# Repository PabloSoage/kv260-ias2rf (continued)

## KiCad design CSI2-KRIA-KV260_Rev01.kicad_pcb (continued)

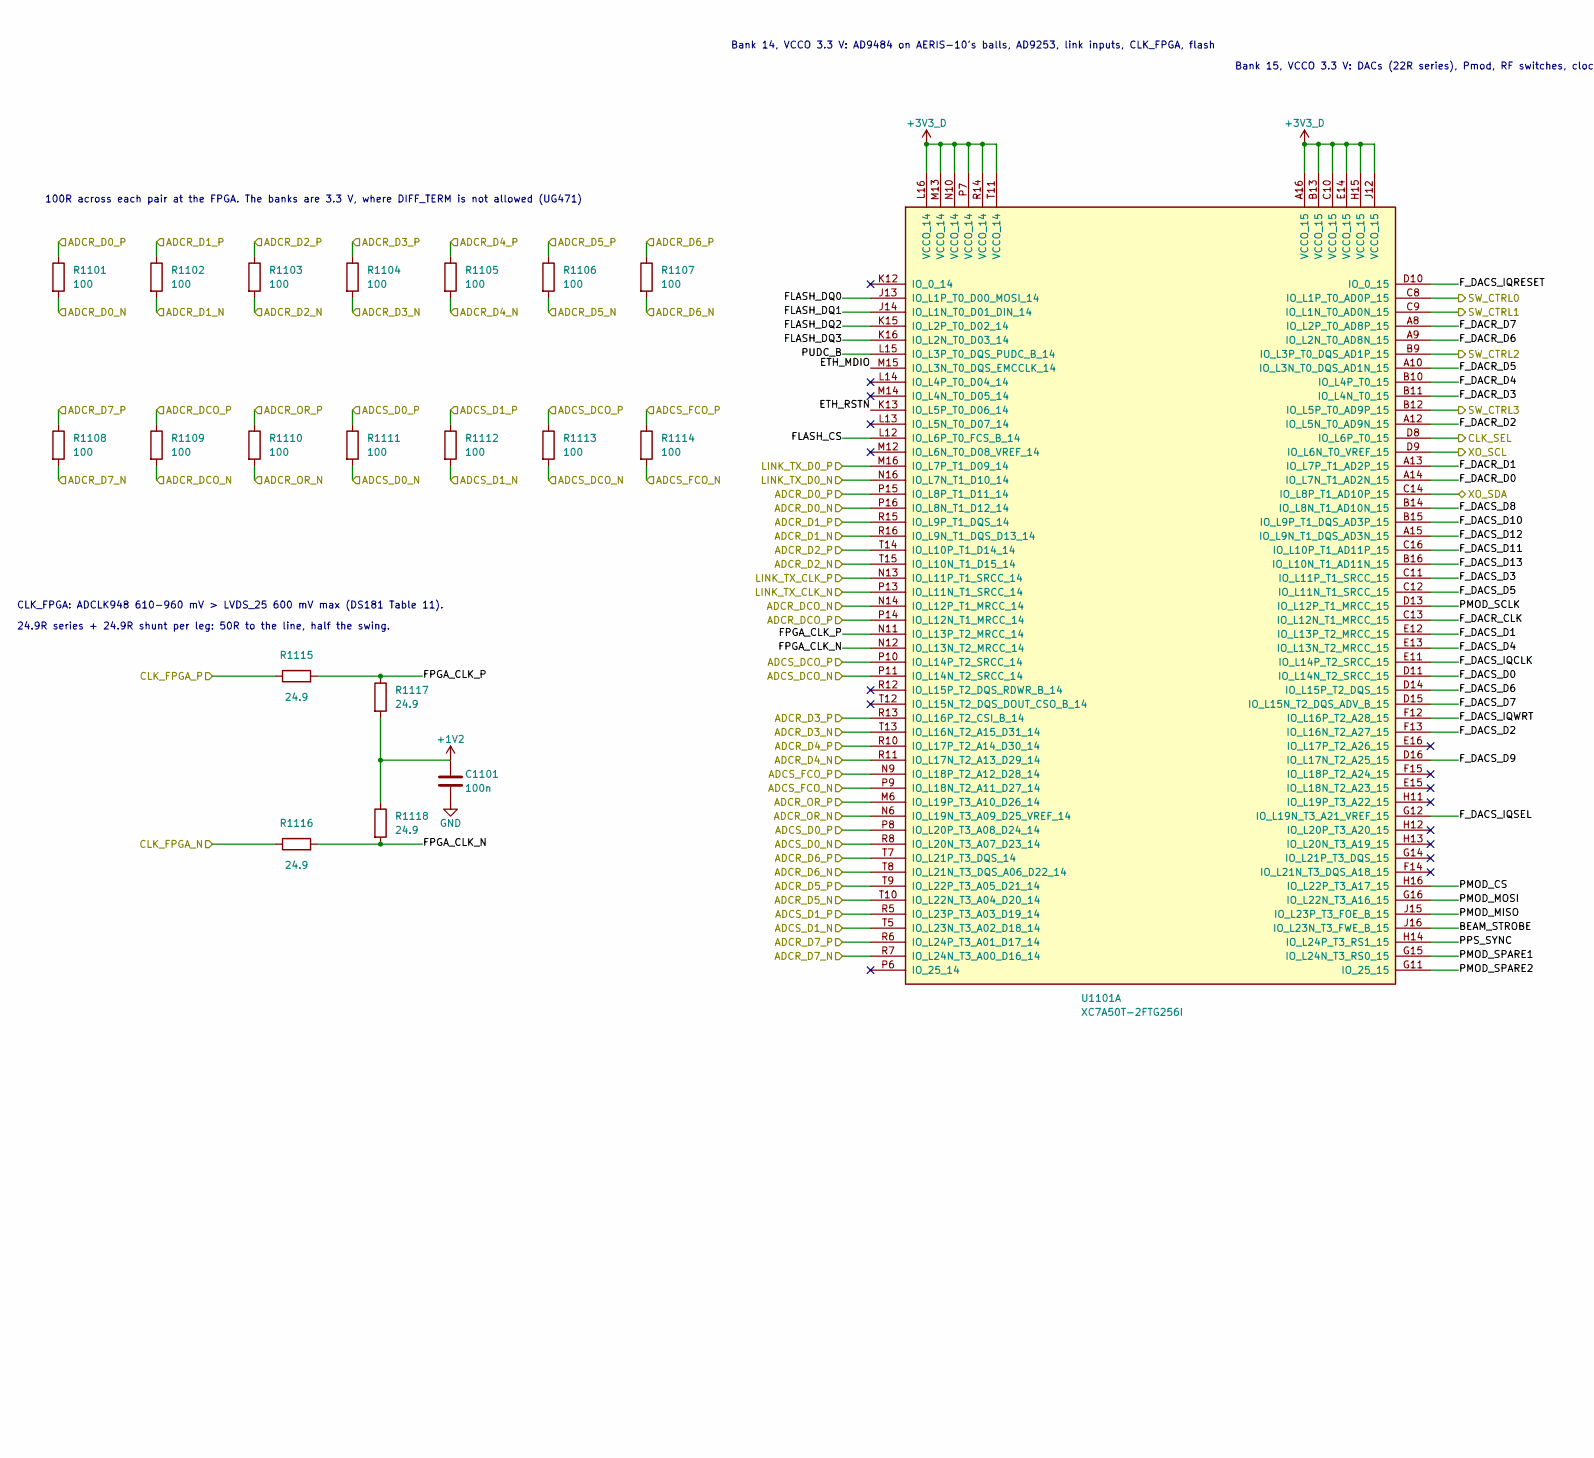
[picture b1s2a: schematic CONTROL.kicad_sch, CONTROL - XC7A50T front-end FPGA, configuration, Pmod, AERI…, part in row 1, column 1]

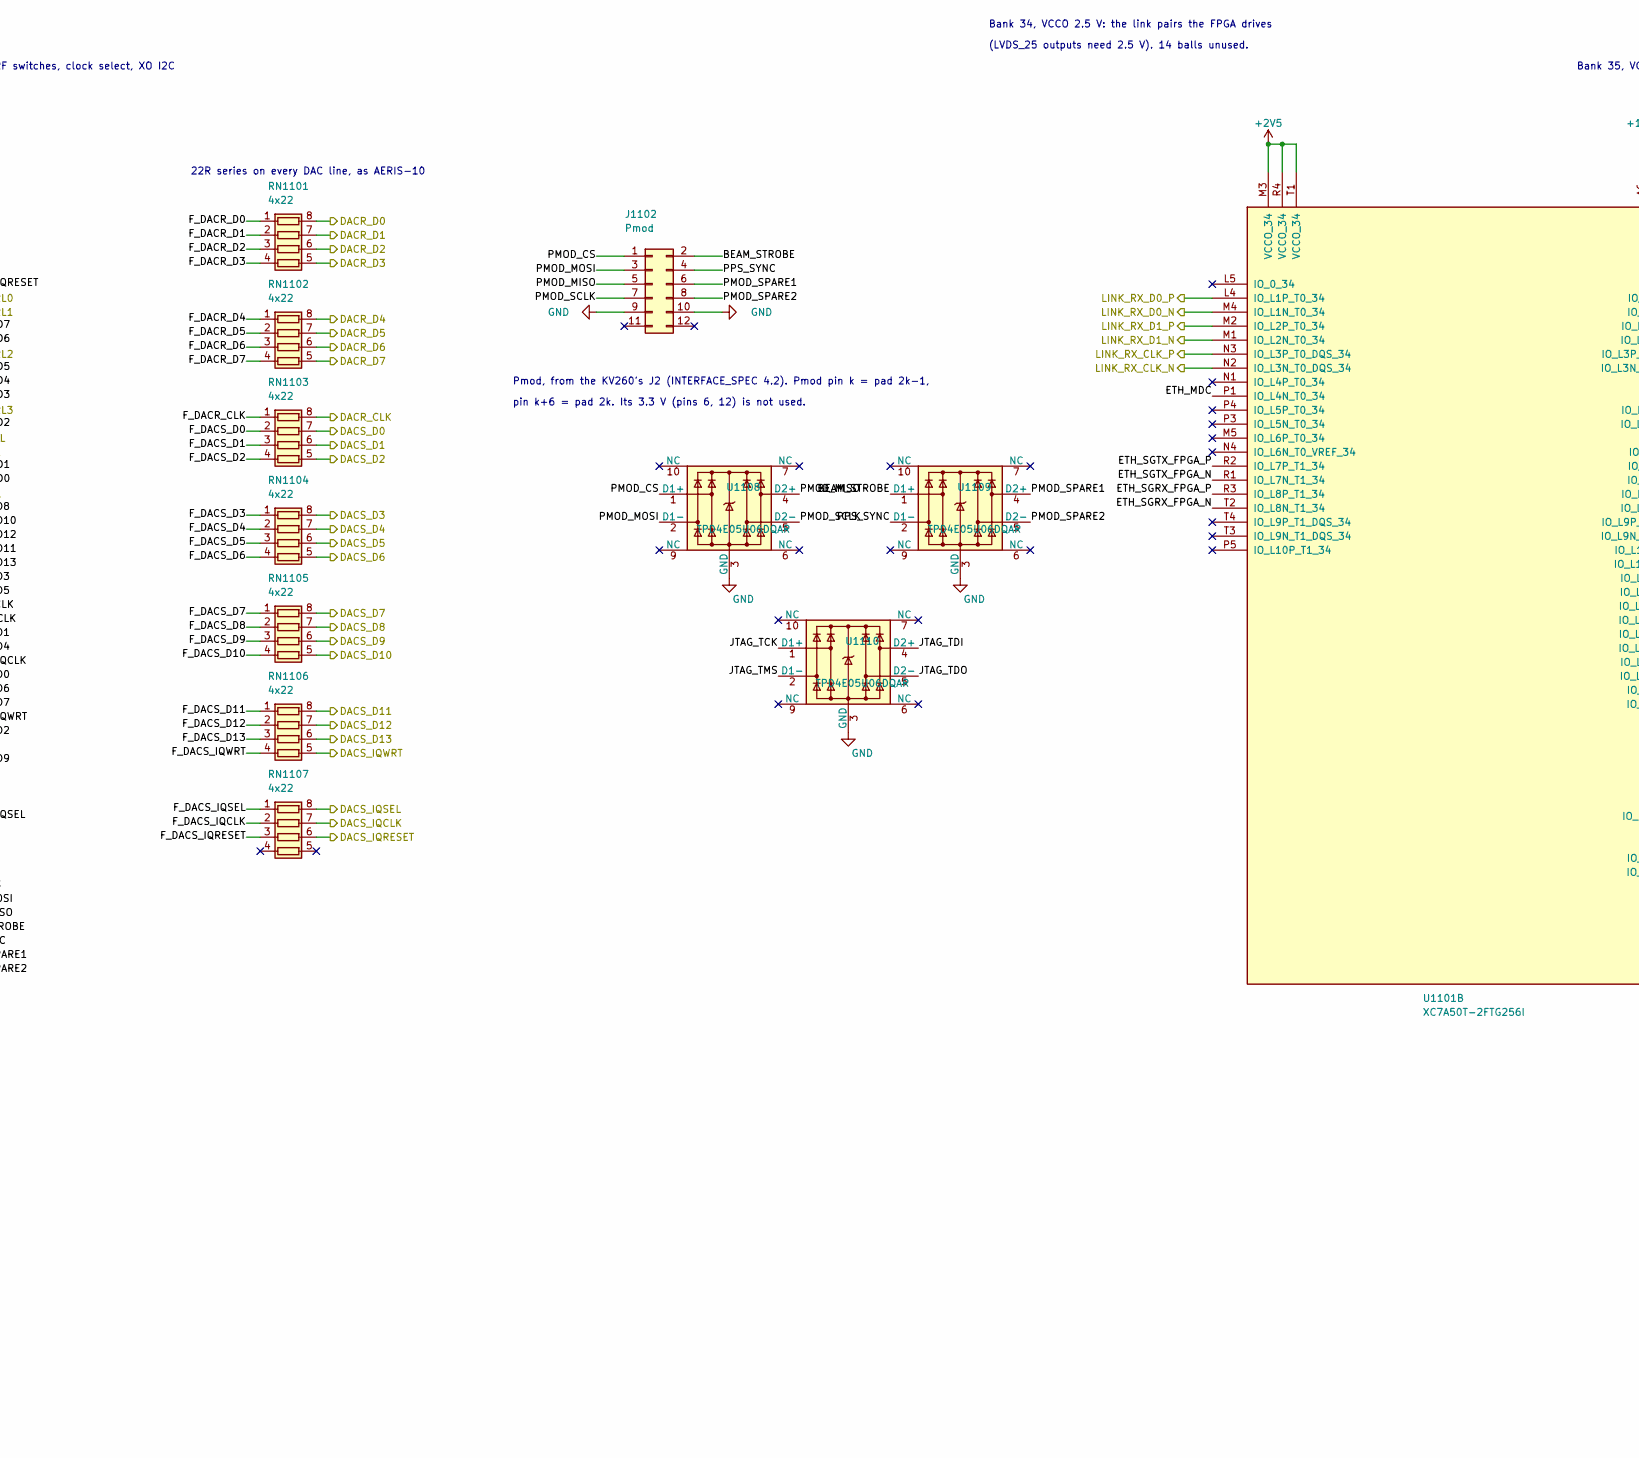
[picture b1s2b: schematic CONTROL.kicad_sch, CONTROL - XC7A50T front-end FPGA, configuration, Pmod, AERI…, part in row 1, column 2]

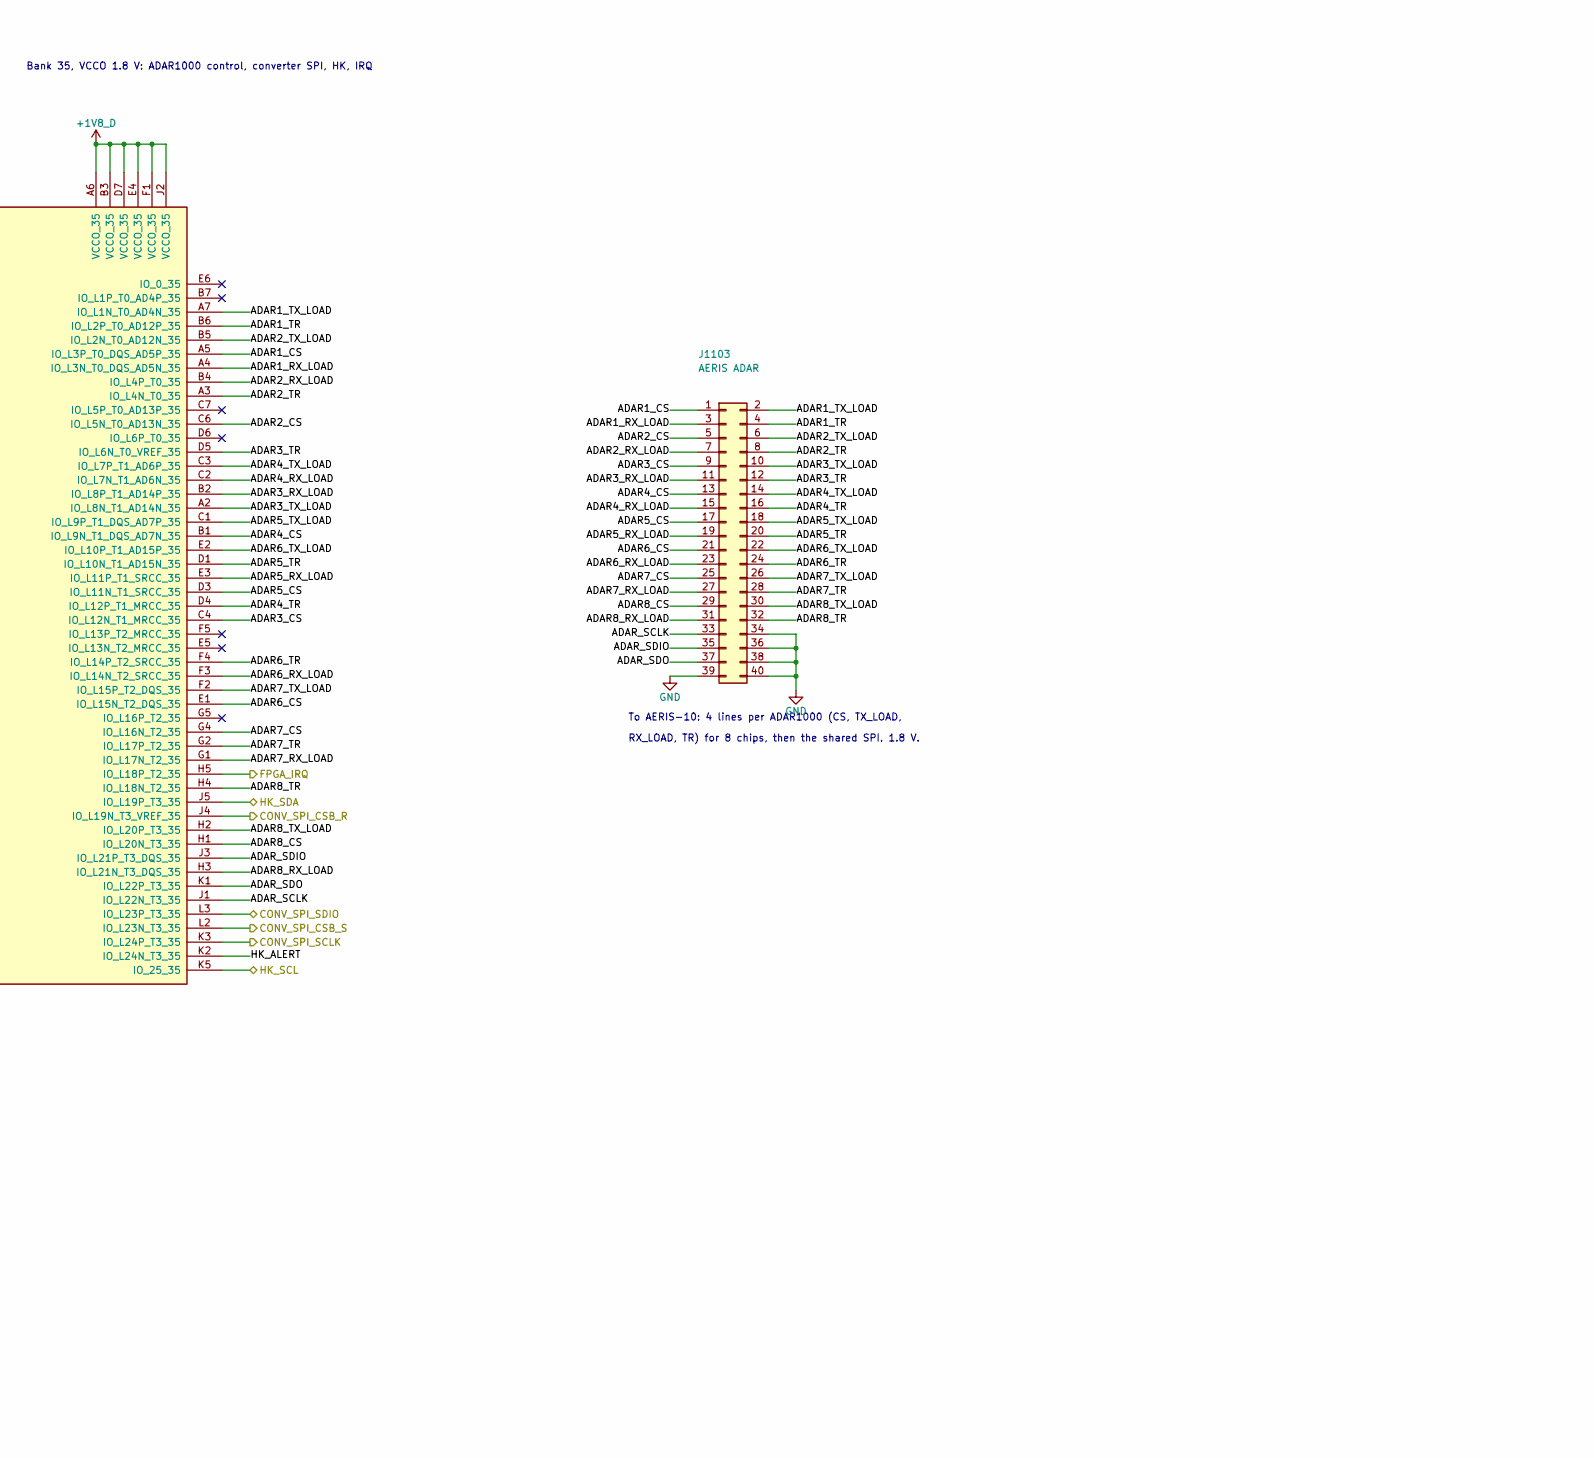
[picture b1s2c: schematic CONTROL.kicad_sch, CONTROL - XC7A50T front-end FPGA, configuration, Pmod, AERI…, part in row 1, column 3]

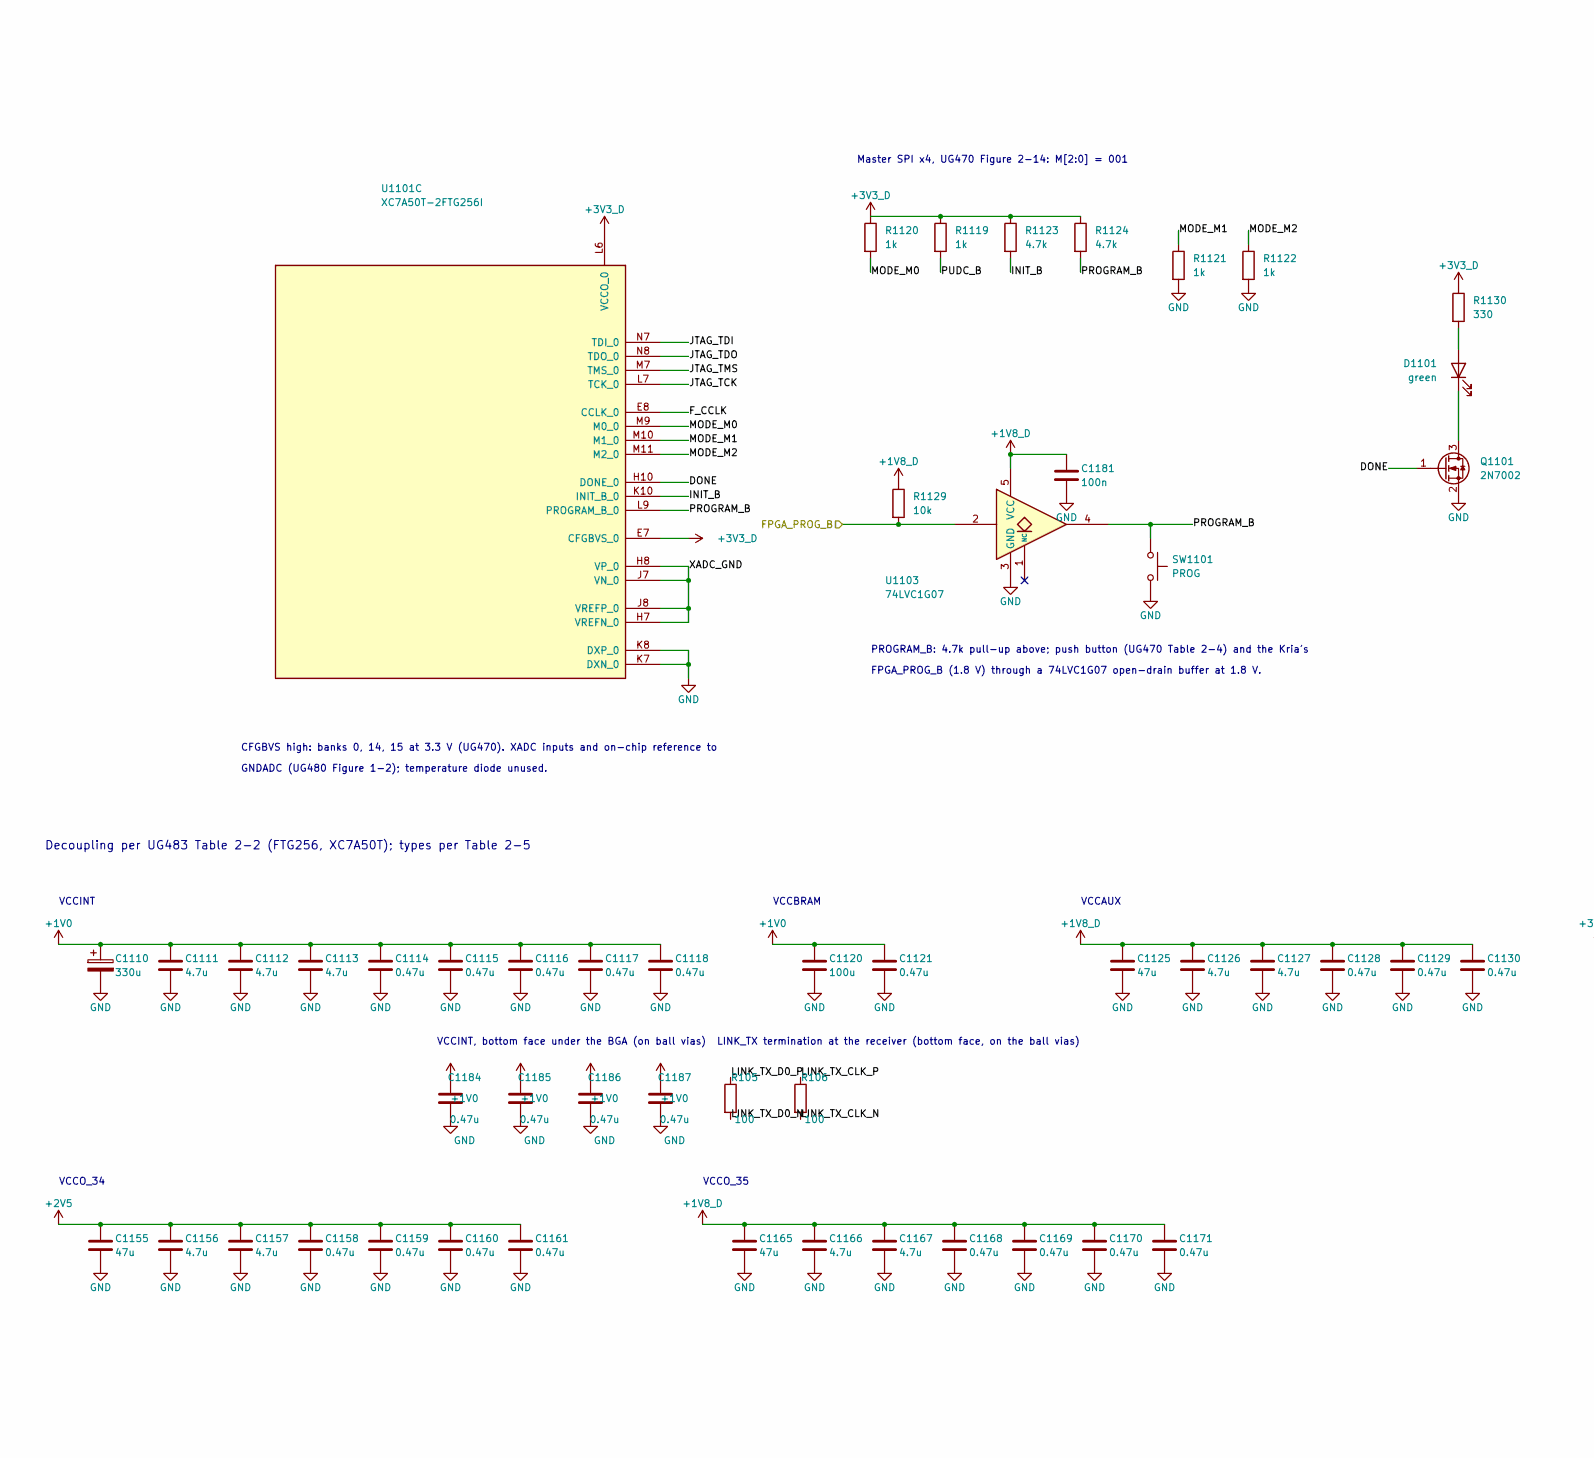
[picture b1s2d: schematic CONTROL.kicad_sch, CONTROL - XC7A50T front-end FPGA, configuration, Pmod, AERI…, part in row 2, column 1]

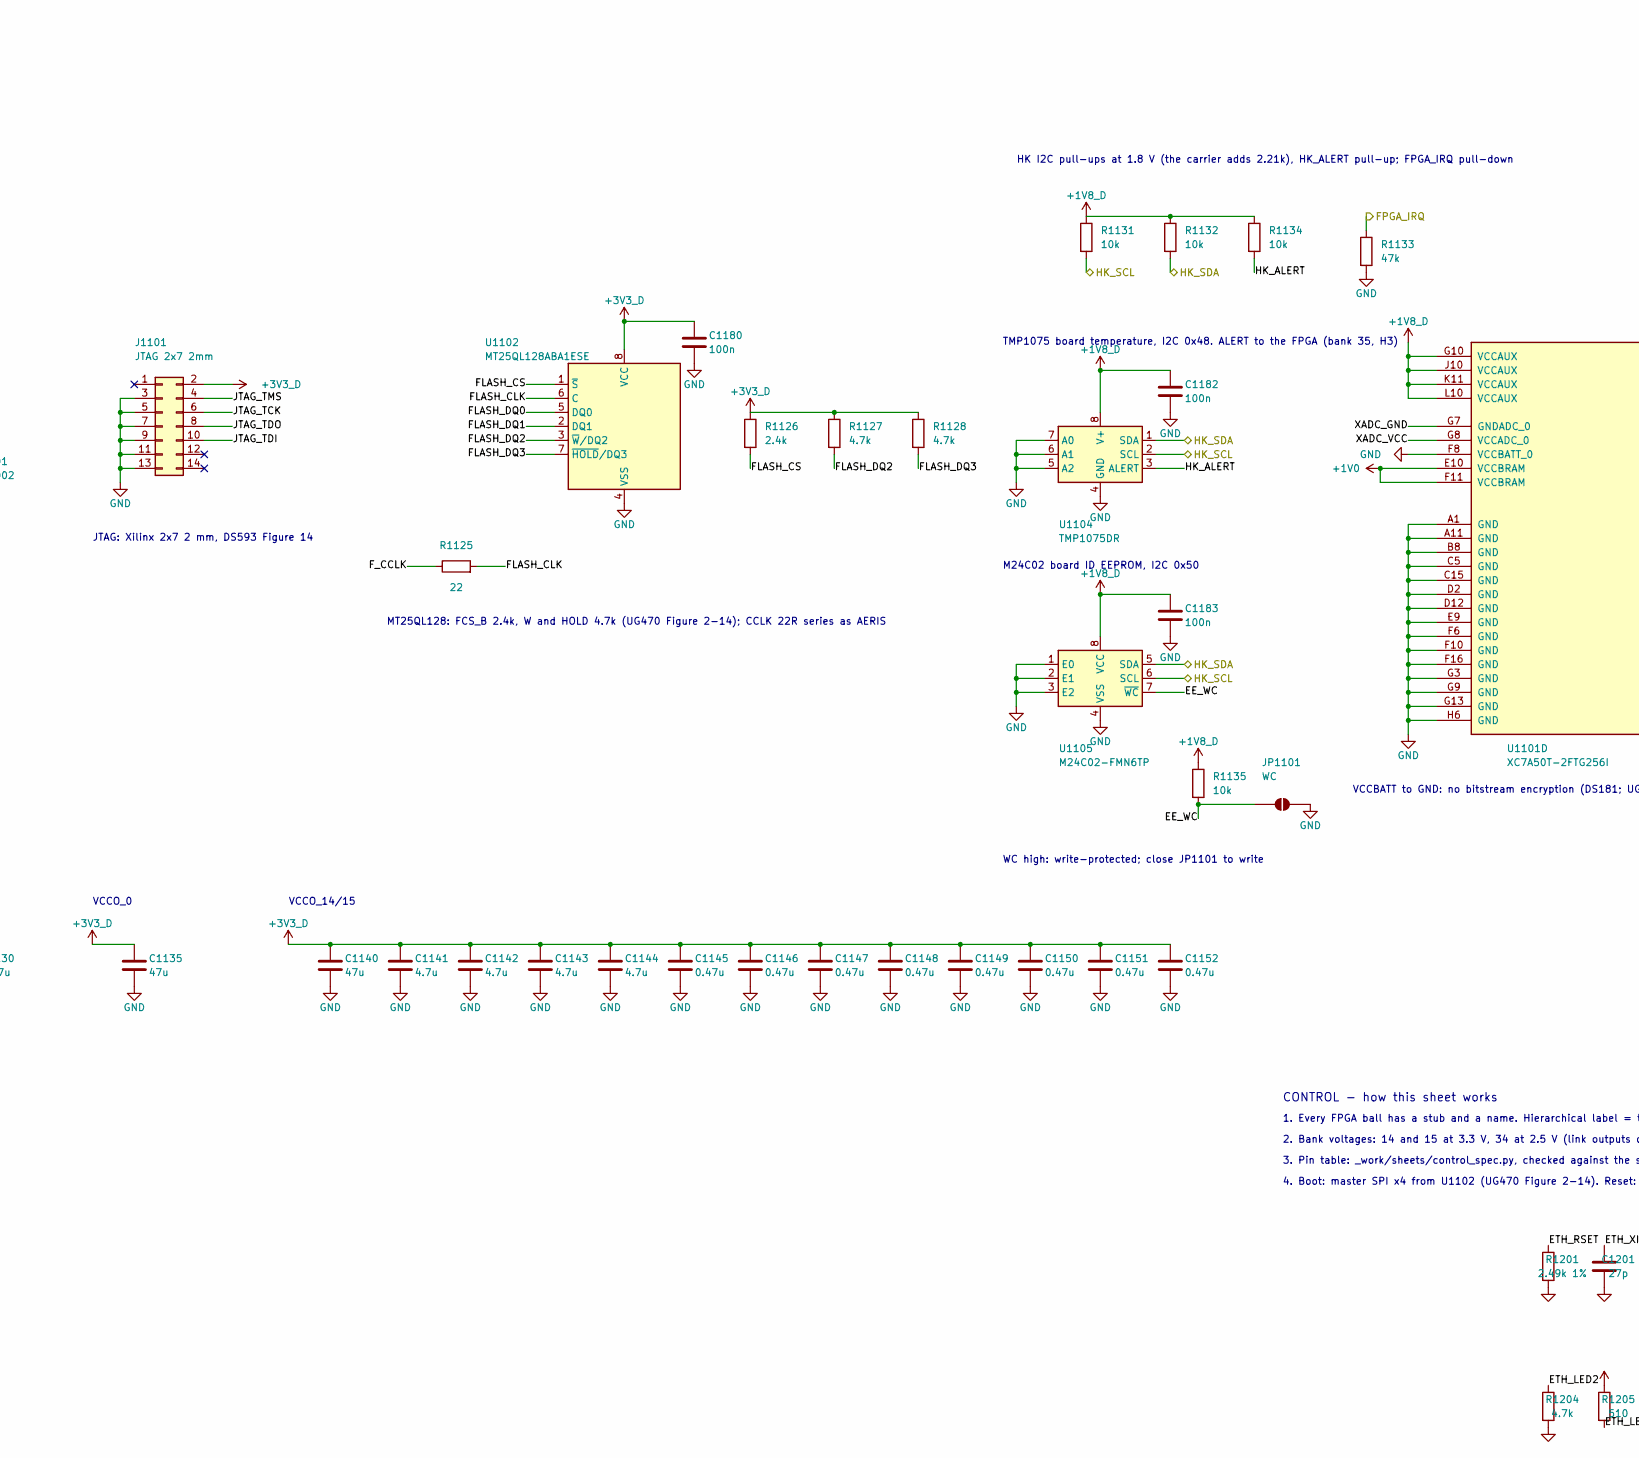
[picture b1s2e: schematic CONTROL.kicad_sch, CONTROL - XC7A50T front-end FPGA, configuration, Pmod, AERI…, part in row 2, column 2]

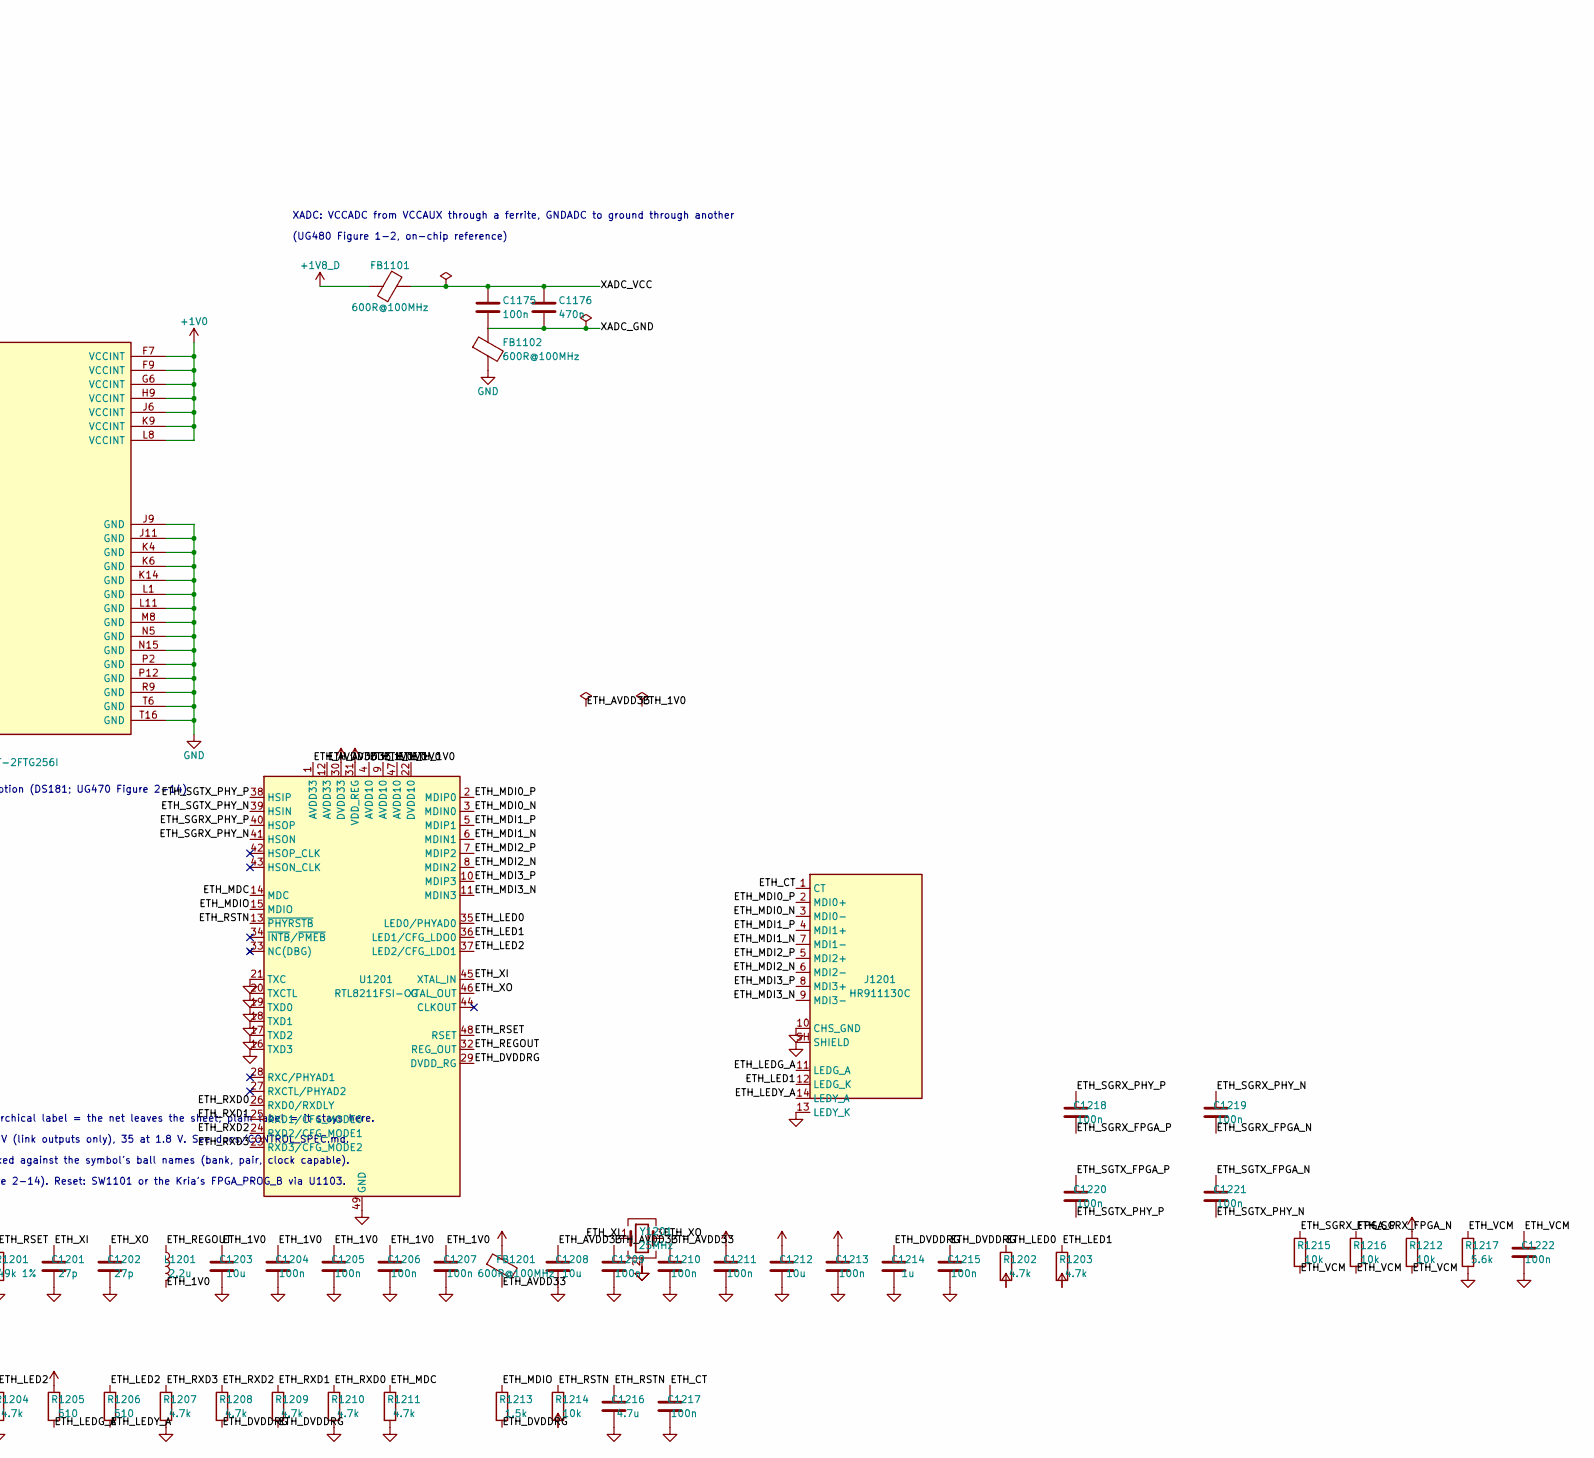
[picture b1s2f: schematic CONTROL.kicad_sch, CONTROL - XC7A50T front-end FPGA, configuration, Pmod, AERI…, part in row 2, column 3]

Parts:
C1101, C1175, C1180, C1181, C1182, C1183, C1204, C1205, C1206, C1207, C1209, C1210, C1211, C1213, C1215, C1217, C1218, C1219, C1220, C1221, C1222: 100n; C_0402_1005Metric
C1110: 330u; CP_EIA-7343-20_Kemet-V
C1111, C1112, C1113, C1126, C1127, C1141, C1142, C1143, C1144, C1156, C1157, C1166, C1167: 4.7u; C_0805_2012Metric
C1114, C1115, C1116, C1117, C1118, C1121, C1128, C1129, C1130, C1145, C1146, C1147, C1148, C1149, C1150, C1151, C1152, C1158, C1159, C1160, C1161, C1168, C1169, C1170, C1171: 0.47u; C_0603_1608Metric
C1120: 100u; C_1210_3225Metric
C1125, C1135, C1140, C1155, C1165: 47u; C_1210_3225Metric
C1176: 470n; C_0603_1608Metric
C1184, C1185, C1186, C1187: 0.47u; C_0402_1005Metric
C1201, C1202: 27p; C_0402_1005Metric
C1203, C1208, C1212: 10u; C_0805_2012Metric
C1214: 1u; C_0402_1005Metric
C1216: 4.7u; C_0402_1005Metric
D1101: green; LED_0603_1608Metric
FB1101, FB1102, FB1201: 600R@100MHz; L_0603_1608Metric
J1101: JTAG 2x7 2mm; PinHeader_2x07_P2.00mm_Vertical
J1102: Pmod; PinHeader_2x06_P2.54mm_Vertical
J1103: AERIS ADAR; IDC-Header_2x20_P2.54mm_Vertical
J1201: HR911130C; RJ45_Hanrun_HR911130C
JP1101: WC; SolderJumper-2_P1.3mm_Open_RoundedPad1.0x1.5mm
L1201: 2.2u; L_0805_2012Metric
Q1101: 2N7002; SOT-23
R105, R106, R1101, R1102, R1103, R1104, R1105, R1106, R1107, R1108, R1109, R1110, R1111, R1112, R1113, R1114: 100; R_0402_1005Metric
R1115, R1116, R1117, R1118: 24.9; R_0402_1005Metric
R1119, R1120, R1121, R1122: 1k; R_0402_1005Metric
R1123, R1124, R1127, R1128, R1202, R1203, R1204, R1207, R1208, R1209, R1210, R1211: 4.7k; R_0402_1005Metric
R1125: 22; R_0402_1005Metric
R1126: 2.4k; R_0402_1005Metric
R1129, R1131, R1132, R1134, R1135, R1212, R1214, R1215, R1216: 10k; R_0402_1005Metric
R1130: 330; R_0402_1005Metric
R1133: 47k; R_0402_1005Metric
R1201: 2.49k 1%; R_0402_1005Metric
R1205, R1206: 510; R_0402_1005Metric
R1213: 1.5k; R_0402_1005Metric
R1217: 5.6k; R_0402_1005Metric
RN1101, RN1102, RN1103, RN1104, RN1105, RN1106, RN1107: 4x22; R_Array_Convex_4x0402
SW1101: PROG; SW_SPST_TL3342
U1101: XC7A50T-2FTG256I; Xilinx_FTG256
U1102: MT25QL128ABA1ESE; SOIC-8_5.3x5.3mm_P1.27mm
U1103: 74LVC1G07; SOT-23-5
U1104: TMP1075DR; SOIC-8_3.9x4.9mm_P1.27mm
U1105: M24C02-FMN6TP; SOIC-8_3.9x4.9mm_P1.27mm
U1108, U1109, U1110: TPD4E05U06DQAR; USON-10_2.5x1.0mm_P0.5mm
U1201: RTL8211FSI-CG; QFN-48-1EP_6x6mm_P0.4mm_EP4.4x4.4mm
Y1201: 25MHz; Crystal_SMD_3225-4Pin_3.2x2.5mm

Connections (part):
+1V0: C1110.1, C1111.1, C1112.1, C1113.1, C1114.1, C1115.1, C1116.1, C1117.1, C1118.1, C1120.1, C1121.1, C1184.1, C1185.1, C1186.1, C1187.1, U1101.E10 (VCCBRAM), U1101.F7 (VCCINT), U1101.F9 (VCCINT), U1101.F11 (VCCBRAM), U1101.G6 (VCCINT), U1101.H9 (VCCINT), U1101.J6 (VCCINT), U1101.K9 (VCCINT), U1101.L8 (VCCINT); also elsewhere on the board
+1V2: C1101.1, R1117.2, R1118.1; also elsewhere on the board
+1V8_D: C1125.1, C1126.1, C1127.1, C1128.1, C1129.1, C1130.1, C1165.1, C1166.1, C1167.1, C1168.1, C1169.1, C1170.1, C1171.1, C1181.1, C1182.1, C1183.1, FB1101.1, R1129.1, R1131.1, R1132.1, R1134.1, R1135.1, U1101.A6 (VCCO_35), U1101.B3 (VCCO_35), U1101.D7 (VCCO_35), U1101.E4 (VCCO_35), U1101.F1 (VCCO_35), U1101.G10 (VCCAUX), U1101.J2 (VCCO_35), U1101.J10 (VCCAUX), U1101.K11 (VCCAUX), U1101.L10 (VCCAUX), U1103.5 (VCC), U1104.8 (V+), U1105.8 (VCC); also elsewhere on the board
+2V5: C1155.1, C1156.1, C1157.1, C1158.1, C1159.1, C1160.1, C1161.1, U1101.M3 (VCCO_34), U1101.R4 (VCCO_34), U1101.T1 (VCCO_34); also elsewhere on the board
+3V3_D: C1135.1, C1140.1, C1141.1, C1142.1, C1143.1, C1144.1, C1145.1, C1146.1, C1147.1, C1148.1, C1149.1, C1150.1, C1151.1, C1152.1, C1180.1, C1211.1, C1212.1, C1213.1, FB1201.1, J1101.2, R1119.1, R1120.1, R1123.1, R1124.1, R1126.1, R1127.1, R1128.1, R1130.1, R1202.2, R1203.2, R1205.1, R1212.1, R1214.2, U1101.A16 (VCCO_15), U1101.B13 (VCCO_15), U1101.C10 (VCCO_15), U1101.E7 (CFGBVS_0), U1101.E14 (VCCO_15), U1101.H15 (VCCO_15), U1101.J12 (VCCO_15), U1101.L6 (VCCO_0), U1101.L16 (VCCO_14), U1101.M13 (VCCO_14), U1101.N10 (VCCO_14), U1101.P7 (VCCO_14), U1101.R14 (VCCO_14), U1101.T11 (VCCO_14), U1102.8 (VCC), U1201.30 (DVDD33), U1201.31 (VDD_REG); also elsewhere on the board
/ADCR_D0_N: R1101.2, U1101.P16 (IO_L8N_T1_D12_14); also elsewhere on the board
/ADCR_D0_P: R1101.1, U1101.P15 (IO_L8P_T1_D11_14); also elsewhere on the board
/ADCR_D1_N: R1102.2, U1101.R16 (IO_L9N_T1_DQS_D13_14); also elsewhere on the board
/ADCR_D1_P: R1102.1, U1101.R15 (IO_L9P_T1_DQS_14); also elsewhere on the board
/ADCR_D2_N: R1103.2, U1101.T15 (IO_L10N_T1_D15_14); also elsewhere on the board
/ADCR_D2_P: R1103.1, U1101.T14 (IO_L10P_T1_D14_14); also elsewhere on the board
/ADCR_D3_N: R1104.2, U1101.T13 (IO_L16N_T2_A15_D31_14); also elsewhere on the board
/ADCR_D3_P: R1104.1, U1101.R13 (IO_L16P_T2_CSI_B_14); also elsewhere on the board
/ADCR_D4_N: R1105.2, U1101.R11 (IO_L17N_T2_A13_D29_14); also elsewhere on the board
/ADCR_D4_P: R1105.1, U1101.R10 (IO_L17P_T2_A14_D30_14); also elsewhere on the board
/ADCR_D5_N: R1106.2, U1101.T10 (IO_L22N_T3_A04_D20_14); also elsewhere on the board
/ADCR_D5_P: R1106.1, U1101.T9 (IO_L22P_T3_A05_D21_14); also elsewhere on the board
/ADCR_D6_N: R1107.2, U1101.T8 (IO_L21N_T3_DQS_A06_D22_14); also elsewhere on the board
/ADCR_D6_P: R1107.1, U1101.T7 (IO_L21P_T3_DQS_14); also elsewhere on the board
/ADCR_D7_N: R1108.2, U1101.R7 (IO_L24N_T3_A00_D16_14); also elsewhere on the board
/ADCR_D7_P: R1108.1, U1101.R6 (IO_L24P_T3_A01_D17_14); also elsewhere on the board
/ADCR_DCO_N: R1109.2, U1101.N14 (IO_L12P_T1_MRCC_14); also elsewhere on the board
/ADCR_DCO_P: R1109.1, U1101.P14 (IO_L12N_T1_MRCC_14); also elsewhere on the board
/ADCR_OR_N: R1110.2, U1101.N6 (IO_L19N_T3_A09_D25_VREF_14); also elsewhere on the board
/ADCR_OR_P: R1110.1, U1101.M6 (IO_L19P_T3_A10_D26_14); also elsewhere on the board
/ADCS_D0_N: R1111.2, U1101.R8 (IO_L20N_T3_A07_D23_14); also elsewhere on the board
/ADCS_D0_P: R1111.1, U1101.P8 (IO_L20P_T3_A08_D24_14); also elsewhere on the board
/ADCS_D1_N: R1112.2, U1101.T5 (IO_L23N_T3_A02_D18_14); also elsewhere on the board
/ADCS_D1_P: R1112.1, U1101.R5 (IO_L23P_T3_A03_D19_14); also elsewhere on the board
/ADCS_DCO_N: R1113.2, U1101.P11 (IO_L14N_T2_SRCC_14); also elsewhere on the board
/ADCS_DCO_P: R1113.1, U1101.P10 (IO_L14P_T2_SRCC_14); also elsewhere on the board
/ADCS_FCO_N: R1114.2, U1101.P9 (IO_L18N_T2_A11_D27_14); also elsewhere on the board
/ADCS_FCO_P: R1114.1, U1101.N9 (IO_L18P_T2_A12_D28_14); also elsewhere on the board
/CLK_FPGA_N: R1116.1; also elsewhere on the board
/CLK_FPGA_P: R1115.1; also elsewhere on the board
/CLK_SEL: U1101.D8 (IO_L6P_T0_15); also elsewhere on the board
/CONTROL/ADAR1_CS: J1103.1, U1101.A5 (IO_L3P_T0_DQS_AD5P_35)
/CONTROL/ADAR1_RX_LOAD: J1103.3, U1101.A4 (IO_L3N_T0_DQS_AD5N_35)
/CONTROL/ADAR1_TR: J1103.4, U1101.B6 (IO_L2P_T0_AD12P_35)
/CONTROL/ADAR1_TX_LOAD: J1103.2, U1101.A7 (IO_L1N_T0_AD4N_35)
/CONTROL/ADAR2_CS: J1103.5, U1101.C6 (IO_L5N_T0_AD13N_35)
/CONTROL/ADAR2_RX_LOAD: J1103.7, U1101.B4 (IO_L4P_T0_35)
/CONTROL/ADAR2_TR: J1103.8, U1101.A3 (IO_L4N_T0_35)
/CONTROL/ADAR2_TX_LOAD: J1103.6, U1101.B5 (IO_L2N_T0_AD12N_35)
/CONTROL/ADAR3_CS: J1103.9, U1101.C4 (IO_L12N_T1_MRCC_35)
/CONTROL/ADAR3_RX_LOAD: J1103.11, U1101.B2 (IO_L8P_T1_AD14P_35)
/CONTROL/ADAR3_TR: J1103.12, U1101.D5 (IO_L6N_T0_VREF_35)
/CONTROL/ADAR3_TX_LOAD: J1103.10, U1101.A2 (IO_L8N_T1_AD14N_35)
/CONTROL/ADAR4_CS: J1103.13, U1101.B1 (IO_L9N_T1_DQS_AD7N_35)
/CONTROL/ADAR4_RX_LOAD: J1103.15, U1101.C2 (IO_L7N_T1_AD6N_35)
/CONTROL/ADAR4_TR: J1103.16, U1101.D4 (IO_L12P_T1_MRCC_35)
/CONTROL/ADAR4_TX_LOAD: J1103.14, U1101.C3 (IO_L7P_T1_AD6P_35)
/CONTROL/ADAR5_CS: J1103.17, U1101.D3 (IO_L11N_T1_SRCC_35)
/CONTROL/ADAR5_RX_LOAD: J1103.19, U1101.E3 (IO_L11P_T1_SRCC_35)
/CONTROL/ADAR5_TR: J1103.20, U1101.D1 (IO_L10N_T1_AD15N_35)
/CONTROL/ADAR5_TX_LOAD: J1103.18, U1101.C1 (IO_L9P_T1_DQS_AD7P_35)
/CONTROL/ADAR6_CS: J1103.21, U1101.E1 (IO_L15N_T2_DQS_35)
/CONTROL/ADAR6_RX_LOAD: J1103.23, U1101.F3 (IO_L14N_T2_SRCC_35)
/CONTROL/ADAR6_TR: J1103.24, U1101.F4 (IO_L14P_T2_SRCC_35)
/CONTROL/ADAR6_TX_LOAD: J1103.22, U1101.E2 (IO_L10P_T1_AD15P_35)
/CONTROL/ADAR7_CS: J1103.25, U1101.G4 (IO_L16N_T2_35)
/CONTROL/ADAR7_RX_LOAD: J1103.27, U1101.G1 (IO_L17N_T2_35)
/CONTROL/ADAR7_TR: J1103.28, U1101.G2 (IO_L17P_T2_35)
/CONTROL/ADAR7_TX_LOAD: J1103.26, U1101.F2 (IO_L15P_T2_DQS_35)
/CONTROL/ADAR8_CS: J1103.29, U1101.H1 (IO_L20N_T3_35)
/CONTROL/ADAR8_RX_LOAD: J1103.31, U1101.H3 (IO_L21N_T3_DQS_35)
/CONTROL/ADAR8_TR: J1103.32, U1101.H4 (IO_L18N_T2_35)
/CONTROL/ADAR8_TX_LOAD: J1103.30, U1101.H2 (IO_L20P_T3_35)
/CONTROL/ADAR_SCLK: J1103.33, U1101.J1 (IO_L22N_T3_35)
/CONTROL/ADAR_SDIO: J1103.35, U1101.J3 (IO_L21P_T3_DQS_35)
/CONTROL/ADAR_SDO: J1103.37, U1101.K1 (IO_L22P_T3_35)
/CONTROL/BEAM_STROBE: J1102.2, U1101.J16 (IO_L23N_T3_FWE_B_15), U1109.1 (D1+)
/CONTROL/DONE: Q1101.1 (G), U1101.H10 (DONE_0); also elsewhere on the board
/CONTROL/EE_WC: JP1101.1 (A), R1135.2, U1105.7 (~WC)
/CONTROL/ETH_1V0: C1203.1, C1204.1, C1205.1, C1206.1, C1207.1, L1201.2, U1201.4 (AVDD10), U1201.9 (AVDD10), U1201.22 (DVDD10), U1201.47 (AVDD10)
/CONTROL/ETH_AVDD33: C1208.1, C1209.1, C1210.1, FB1201.2, U1201.1 (AVDD33), U1201.12 (AVDD33)
/CONTROL/ETH_CT: C1217.1, J1201.1 (CT)
/CONTROL/ETH_DVDDRG: C1214.1, C1215.1, R1208.2, R1209.2, R1213.2, U1201.29 (DVDD_RG)
/CONTROL/ETH_LED0: R1202.1, U1201.35 (LED0/PHYAD0)
/CONTROL/ETH_LED1: J1201.12 (LEDG_K), R1203.1, U1201.36 (LED1/CFG_LDO0)
/CONTROL/ETH_LED2: R1204.1, R1206.1, U1201.37 (LED2/CFG_LDO1)
/CONTROL/ETH_LEDG_A: J1201.11 (LEDG_A), R1205.2
/CONTROL/ETH_LEDY_A: J1201.14 (LEDY_A), R1206.2
/CONTROL/ETH_MDC: R1211.1, U1101.P1 (IO_L4N_T0_34), U1201.14 (MDC); also elsewhere on the board
/CONTROL/ETH_MDI0_N: J1201.3 (MDI0-), U1201.3 (MDIN0)
/CONTROL/ETH_MDI0_P: J1201.2 (MDI0+), U1201.2 (MDIP0)
/CONTROL/ETH_MDI1_N: J1201.7 (MDI1-), U1201.6 (MDIN1)
/CONTROL/ETH_MDI1_P: J1201.4 (MDI1+), U1201.5 (MDIP1)
/CONTROL/ETH_MDI2_N: J1201.6 (MDI2-), U1201.8 (MDIN2)
/CONTROL/ETH_MDI2_P: J1201.5 (MDI2+), U1201.7 (MDIP2)
/CONTROL/ETH_MDI3_N: J1201.9 (MDI3-), U1201.11 (MDIN3)
/CONTROL/ETH_MDI3_P: J1201.8 (MDI3+), U1201.10 (MDIP3)
/CONTROL/ETH_MDIO: R1213.1, U1101.M15 (IO_L3N_T0_DQS_EMCCLK_14), U1201.15 (MDIO); also elsewhere on the board
/CONTROL/ETH_REGOUT: L1201.1, U1201.32 (REG_OUT)
/CONTROL/ETH_RSET: R1201.1, U1201.48 (RSET)
/CONTROL/ETH_RSTN: C1216.1, R1214.1, U1101.K13 (IO_L5P_T0_D06_14), U1201.13 (~PHYRSTB)
/CONTROL/ETH_RXD0: R1210.1, U1201.26 (RXD0/RXDLY)
/CONTROL/ETH_RXD1: R1209.1, U1201.25 (RXD1/CFG_MODE0)
/CONTROL/ETH_RXD2: R1208.1, U1201.24 (RXD2/CFG_MODE1)
/CONTROL/ETH_RXD3: R1207.1, U1201.23 (RXD3/CFG_MODE2)
/CONTROL/ETH_SGRX_FPGA_N: C1219.2, R1216.1, U1101.T2 (IO_L8N_T1_34)
/CONTROL/ETH_SGRX_FPGA_P: C1218.2, R1215.1, U1101.R3 (IO_L8P_T1_34)
/CONTROL/ETH_SGRX_PHY_N: C1219.1, U1201.41 (HSON)
/CONTROL/ETH_SGRX_PHY_P: C1218.1, U1201.40 (HSOP)
/CONTROL/ETH_SGTX_FPGA_N: C1221.1, U1101.R1 (IO_L7N_T1_34)
/CONTROL/ETH_SGTX_FPGA_P: C1220.1, U1101.R2 (IO_L7P_T1_34)
/CONTROL/ETH_SGTX_PHY_N: C1221.2, U1201.39 (HSIN)
/CONTROL/ETH_SGTX_PHY_P: C1220.2, U1201.38 (HSIP)
/CONTROL/ETH_VCM: C1222.1, R1212.2, R1215.2, R1216.2, R1217.1
/CONTROL/ETH_XI: C1201.1, U1201.45 (XTAL_IN), Y1201.1
/CONTROL/ETH_XO: C1202.1, U1201.46 (XTAL_OUT), Y1201.3
/CONTROL/FLASH_CLK: R1125.2, U1102.6 (C)
/CONTROL/FLASH_CS: R1126.2, U1101.L12 (IO_L6P_T0_FCS_B_14), U1102.1 (~S)
/CONTROL/FLASH_DQ0: U1101.J13 (IO_L1P_T0_D00_MOSI_14), U1102.5 (DQ0)
/CONTROL/FLASH_DQ1: U1101.J14 (IO_L1N_T0_D01_DIN_14), U1102.2 (DQ1)
/CONTROL/FLASH_DQ2: R1127.2, U1101.K15 (IO_L2P_T0_D02_14), U1102.3 (~W/DQ2)
/CONTROL/FLASH_DQ3: R1128.2, U1101.K16 (IO_L2N_T0_D03_14), U1102.7 (~HOLD/DQ3)
/CONTROL/FPGA_CLK_N: R1116.2, R1118.2, U1101.N12 (IO_L13N_T2_MRCC_14)
/CONTROL/FPGA_CLK_P: R1115.2, R1117.1, U1101.N11 (IO_L13P_T2_MRCC_14)
/CONTROL/F_CCLK: R1125.1, U1101.E8 (CCLK_0)
/CONTROL/F_DACR_CLK: RN1103.1 (R1.1), U1101.C13 (IO_L12N_T1_MRCC_15)
/CONTROL/F_DACR_D0: RN1101.1 (R1.1), U1101.A14 (IO_L7N_T1_AD2N_15)
/CONTROL/F_DACR_D1: RN1101.2 (R2.1), U1101.A13 (IO_L7P_T1_AD2P_15)
/CONTROL/F_DACR_D2: RN1101.3 (R3.1), U1101.A12 (IO_L5N_T0_AD9N_15)
/CONTROL/F_DACR_D3: RN1101.4 (R4.1), U1101.B11 (IO_L4N_T0_15)
/CONTROL/F_DACR_D4: RN1102.1 (R1.1), U1101.B10 (IO_L4P_T0_15)
/CONTROL/F_DACR_D5: RN1102.2 (R2.1), U1101.A10 (IO_L3N_T0_DQS_AD1N_15)
/CONTROL/F_DACR_D6: RN1102.3 (R3.1), U1101.A9 (IO_L2N_T0_AD8N_15)
/CONTROL/F_DACR_D7: RN1102.4 (R4.1), U1101.A8 (IO_L2P_T0_AD8P_15)
/CONTROL/F_DACS_D0: RN1103.2 (R2.1), U1101.D11 (IO_L14N_T2_SRCC_15)
/CONTROL/F_DACS_D1: RN1103.3 (R3.1), U1101.E12 (IO_L13P_T2_MRCC_15)
/CONTROL/F_DACS_D2: RN1103.4 (R4.1), U1101.F13 (IO_L16N_T2_A27_15)
/CONTROL/F_DACS_D3: RN1104.1 (R1.1), U1101.C11 (IO_L11P_T1_SRCC_15)
/CONTROL/F_DACS_D4: RN1104.2 (R2.1), U1101.E13 (IO_L13N_T2_MRCC_15)
/CONTROL/F_DACS_D5: RN1104.3 (R3.1), U1101.C12 (IO_L11N_T1_SRCC_15)
/CONTROL/F_DACS_D6: RN1104.4 (R4.1), U1101.D14 (IO_L15P_T2_DQS_15)
/CONTROL/F_DACS_D7: RN1105.1 (R1.1), U1101.D15 (IO_L15N_T2_DQS_ADV_B_15)
/CONTROL/F_DACS_D8: RN1105.2 (R2.1), U1101.B14 (IO_L8N_T1_AD10N_15)
/CONTROL/F_DACS_D9: RN1105.3 (R3.1), U1101.D16 (IO_L17N_T2_A25_15)
/CONTROL/F_DACS_D10: RN1105.4 (R4.1), U1101.B15 (IO_L9P_T1_DQS_AD3P_15)
/CONTROL/F_DACS_D11: RN1106.1 (R1.1), U1101.C16 (IO_L10P_T1_AD11P_15)
/CONTROL/F_DACS_D12: RN1106.2 (R2.1), U1101.A15 (IO_L9N_T1_DQS_AD3N_15)
/CONTROL/F_DACS_D13: RN1106.3 (R3.1), U1101.B16 (IO_L10N_T1_AD11N_15)
/CONTROL/F_DACS_IQCLK: RN1107.2 (R2.1), U1101.E11 (IO_L14P_T2_SRCC_15)
/CONTROL/F_DACS_IQRESET: RN1107.3 (R3.1), U1101.D10 (IO_0_15)
/CONTROL/F_DACS_IQSEL: RN1107.1 (R1.1), U1101.G12 (IO_L19N_T3_A21_VREF_15)
/CONTROL/F_DACS_IQWRT: RN1106.4 (R4.1), U1101.F12 (IO_L16P_T2_A28_15)
/CONTROL/HK_ALERT: R1134.2, U1101.K2 (IO_L24N_T3_35), U1104.3 (ALERT)
/CONTROL/INIT_B: R1123.2, U1101.K10 (INIT_B_0)
/CONTROL/JTAG_TCK: J1101.6, U1101.L7 (TCK_0), U1110.1 (D1+)
/CONTROL/JTAG_TDI: J1101.10, U1101.N7 (TDI_0), U1110.4 (D2+)
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
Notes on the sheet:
Bank 14, VCCO 3.3 V: AD9484 on AERIS-10's balls, AD9253, link inputs, CLK_FPGA, flash
Bank 15, VCCO 3.3 V: DACs (22R series), Pmod, RF switches, clock select, XO I2C
100R across each pair at the FPGA. The banks are 3.3 V, where DIFF_TERM is not allowed (UG471)
CLK_FPGA: ADCLK948 610-960 mV > LVDS_25 600 mV max (DS181 Table 11).
24.9R series + 24.9R shunt per leg: 50R to the line, half the swing.
22R series on every DAC line, as AERIS-10
Pmod, from the KV260's J2 (INTERFACE_SPEC 4.2). Pmod pin k = pad 2k-1,
pin k+6 = pad 2k. Its 3.3 V (pins 6, 12) is not used.
Bank 34, VCCO 2.5 V: the link pairs the FPGA drives
(LVDS_25 outputs need 2.5 V). 14 balls unused.
Bank 35, VCCO 1.8 V: ADAR1000 control, converter SPI, HK, IRQ
To AERIS-10: 4 lines per ADAR1000 (CS, TX_LOAD,
RX_LOAD, TR) for 8 chips, then the shared SPI. 1.8 V.
CFGBVS high: banks 0, 14, 15 at 3.3 V (UG470). XADC inputs and on-chip reference to
GNDADC (UG480 Figure 1-2); temperature diode unused.
Master SPI x4, UG470 Figure 2-14: M[2:0] = 001
PROGRAM_B: 4.7k pull-up above; push button (UG470 Table 2-4) and the Kria's
FPGA_PROG_B (1.8 V) through a 74LVC1G07 open-drain buffer at 1.8 V.
JTAG: Xilinx 2x7 2 mm, DS593 Figure 14
MT25QL128: FCS_B 2.4k, W and HOLD 4.7k (UG470 Figure 2-14); CCLK 22R series as AERIS
HK I2C pull-ups at 1.8 V (the carrier adds 2.21k), HK_ALERT pull-up; FPGA_IRQ pull-down
TMP1075 board temperature, I2C 0x48. ALERT to the FPGA (bank 35, H3)
M24C02 board ID EEPROM, I2C 0x50
WC high: write-protected; close JP1101 to write
VCCBATT to GND: no bitstream encryption (DS181; UG470 Figure 2-14)
XADC: VCCADC from VCCAUX through a ferrite, GNDADC to ground through another
(UG480 Figure 1-2, on-chip reference)
Decoupling per UG483 Table 2-2 (FTG256, XC7A50T); types per Table 2-5
VCCINT
VCCBRAM
VCCAUX
VCCO_0
VCCO_14/15
VCCO_34
VCCO_35
CONTROL - how this sheet works
1. Every FPGA ball has a stub and a name. Hierarchical label = the net leaves the sheet; plain label = it stays here.
2. Bank voltages: 14 and 15 at 3.3 V, 34 at 2.5 V (link outputs only), 35 at 1.8 V. See docs/CONTROL_SPEC.md.
3. Pin table: _work/sheets/control_spec.py, checked against the symbol's ball names (bank, pair, clock capable).
4. Boot: master SPI x4 from U1102 (UG470 Figure 2-14). Reset: SW1101 or the Kria's FPGA_PROG_B via U1103.
